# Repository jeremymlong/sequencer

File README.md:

# Sequencer
Inspired by the [LMNC Arduino 8 Step Sequencer Keyboard](https://www.lookmumnocomputer.com/sequencer-keyboard), but with several additional features.

## Specs
 * 0 to 5V range
 * Arduino Nano based
 * Selectable dual 8 steps or 16 steps
 * Arcade button style keyboard
 * Internal or external clock
 * Gate on/off selectable for every step
 * Gate output for every step
 * Reset input and switch
 * Selectable patterns
    * Off
    * Forward
    * Backward
    * Random
    * 1-2-3-4-3-2
    * 1-2-3-4-4-3-2-1
    * Forward 2x (1-1-2-2-3-3-4-4)
    * Backward 2x (4-4-3-3-2-2-1-1)
    * Clockwise
    * Counterclockwise

## BOM
| Part | Quantity | Link |
|------|------|------|
| Arduino Nano | 1 | [Tayda](https://www.taydaelectronics.com/nano-3-0-controller-compatible-with-arduino-nano-usb-driver.html) |
| CD4051 | 1 | [Tayda](https://www.taydaelectronics.com/cd4051-4051-ic-cmos-multiplex-demultiplexer.html) |
| 74HC595 | 2 | [Tayda](https://www.taydaelectronics.com/74hc595-8-bit-shift-register-ic.html) |
| Arcade button | 8 | [Amazon](https://a.co/d/00wVvfu) |
| Mini toggle SPDT | 2 | [Tayda](https://www.taydaelectronics.com/mini-toggle-switch-spdt-on-on.html) |
| Mini toggle SPDT (momentary) | 2 | [Tayda](https://www.taydaelectronics.com/momentary-mini-toggle-switch-spdt-on-off-on.html) |
| Mini toggle DPDT | 1 | [Tayda](https://www.taydaelectronics.com/mini-toggle-switch-dpdt-on-on.html) |
| 100nF Capacitor | 3 | [Tayda](https://www.taydaelectronics.com/0-1uf-100v-5-polyester-film-box-type-capacitor.html) |
| 1N4148 diode | 23 | [Tayda](https://www.taydaelectronics.com/1n4148-switching-signal-diode.html) |
| 5mm WS2811 F5 LED | 20 | [AliExpress](https://www.aliexpress.us/item/2251832527100547.html?gatewayAdapt=glo2usa4itemAdapt), [ebay](https://www.ebay.com/itm/225210423475?itmmeta=01HS53S4ZVHJHBY52T8WQZB1ET&hash=item346f9658b3:g:pUQAAOSwwGdf8ocz&itmprp=enc%3AAQAJAAAAwCDUYGcz5qj68xjJYhneY0VaI0AsSksXRR7zNsdxxVYPv%2BTpHbM6i6Cse7igi7r5pkI4ketezPmbqDTaU3huAlq58YY7W5qptqD56XkPZG7GSnOwLtegVyQoB51Hfvr%2BzgxCyjLdDuAnd0qzc8QuIPkxoM4O4NsTp0nrkO%2FBAysmSOFaF0JAeZIQaoKVNi9e1xnuLqgQoH9CKrZYwR4DYm8v4WXOQEnFtDER7cRtcld9aYo08zqe6yW89MqrQOQFFA%3D%3D%7Ctkp%3ABk9SR4jQ5KPJYw) |
| 12 position rotary switch | 1 | [Tayda](https://www.taydaelectronics.com/rotary-switch-1-pole-12-position-alpha-sr2611f.html) |
| 1k Resistor | 1 | [Tayda](https://www.taydaelectronics.com/10-x-resistor-1k-ohm-1-4w-1-metal-film-pkg-of-10.html) |
| 2k Resistor | 11 | [Tayda](https://www.taydaelectronics.com/resistor-2k-ohm-1-4w-1-metal-film-pkg-of-10.html) |
| 10k Resistor | 1 | [Tayda](https://www.taydaelectronics.com/10-x-resistor-10k-ohm-1-4w-1-metal-film-pkg-of-10.html) |
| 100k Resistor | 2 | [Tayda](https://www.taydaelectronics.com/10-x-resistor-100k-ohm-1-4w-1-metal-film-pkg-of-10.html) |
| 470k Resistor | 2 | [Tayda](https://www.taydaelectronics.com/10-x-resistor-470k-ohm-1-4w-1-metal-film-pkg-of-10.html) |
| 100k potentiometer | 17 | [Tayda](https://www.taydaelectronics.com/tayda-100k-ohm-linear-taper-potentiometer-with-solder-lugs.html) (panel wiring) |
| Mono jack | 7 (23 for per gate output) | [Tayda](https://www.taydaelectronics.com/pj-3001f-3-5-mm-mono-phone-jack.html) (pcb), [Tayda](https://www.taydaelectronics.com/3-5mm-earphone-mono-plug.html) (panel wiring) |
| Knobs | 18 |

## TODO
 * Arp when more than 1 button is held
 * Adjustable gate length

## Arduino Dependencies
 * [Adafruit_NeoPixel](https://github.com/adafruit/Adafruit_NeoPixel)

## Note about the schematic and board
Because this is big, I only did a small PCB for this. This is why there are random components floating above the board. For the remaining components (pots, buttons, switches, LEDs) I wired them old school with panel wiring. It was a great reminder why it's so much better to use a PCB for that instead.

## Note about 12 position switch
The 12 position switch is not on the schematic. It's wired like a potentiometer, with the 11 2k resistors between the positions. There are several tutorials on how to do this.

## Note about LEDs
The LEDs are not included on the schematic. I directly mounted the LEDs to the panel with hot glue and wired them point to point. Wires are connected to the leads of the first LED. The LEDs need to be wired in a particular order, as follows:
1. Step 1
1. Step 2
1. Step 3
1. Step 4
1. Step 5
1. Step 6
1. Step 7
1. Step 8
1. Step 16
1. Step 15
1. Step 14
1. Step 13
1. Step 12
1. Step 11
1. Step 10
1. Step 9
1. Clock out
1. Clock in
1. Gate A
1. Gate B

## Note about power
This really needs a clean power source. I'm powering mine from my rack's supply. If I power it from a regular cheap 5V switching adapter, it's noisy.

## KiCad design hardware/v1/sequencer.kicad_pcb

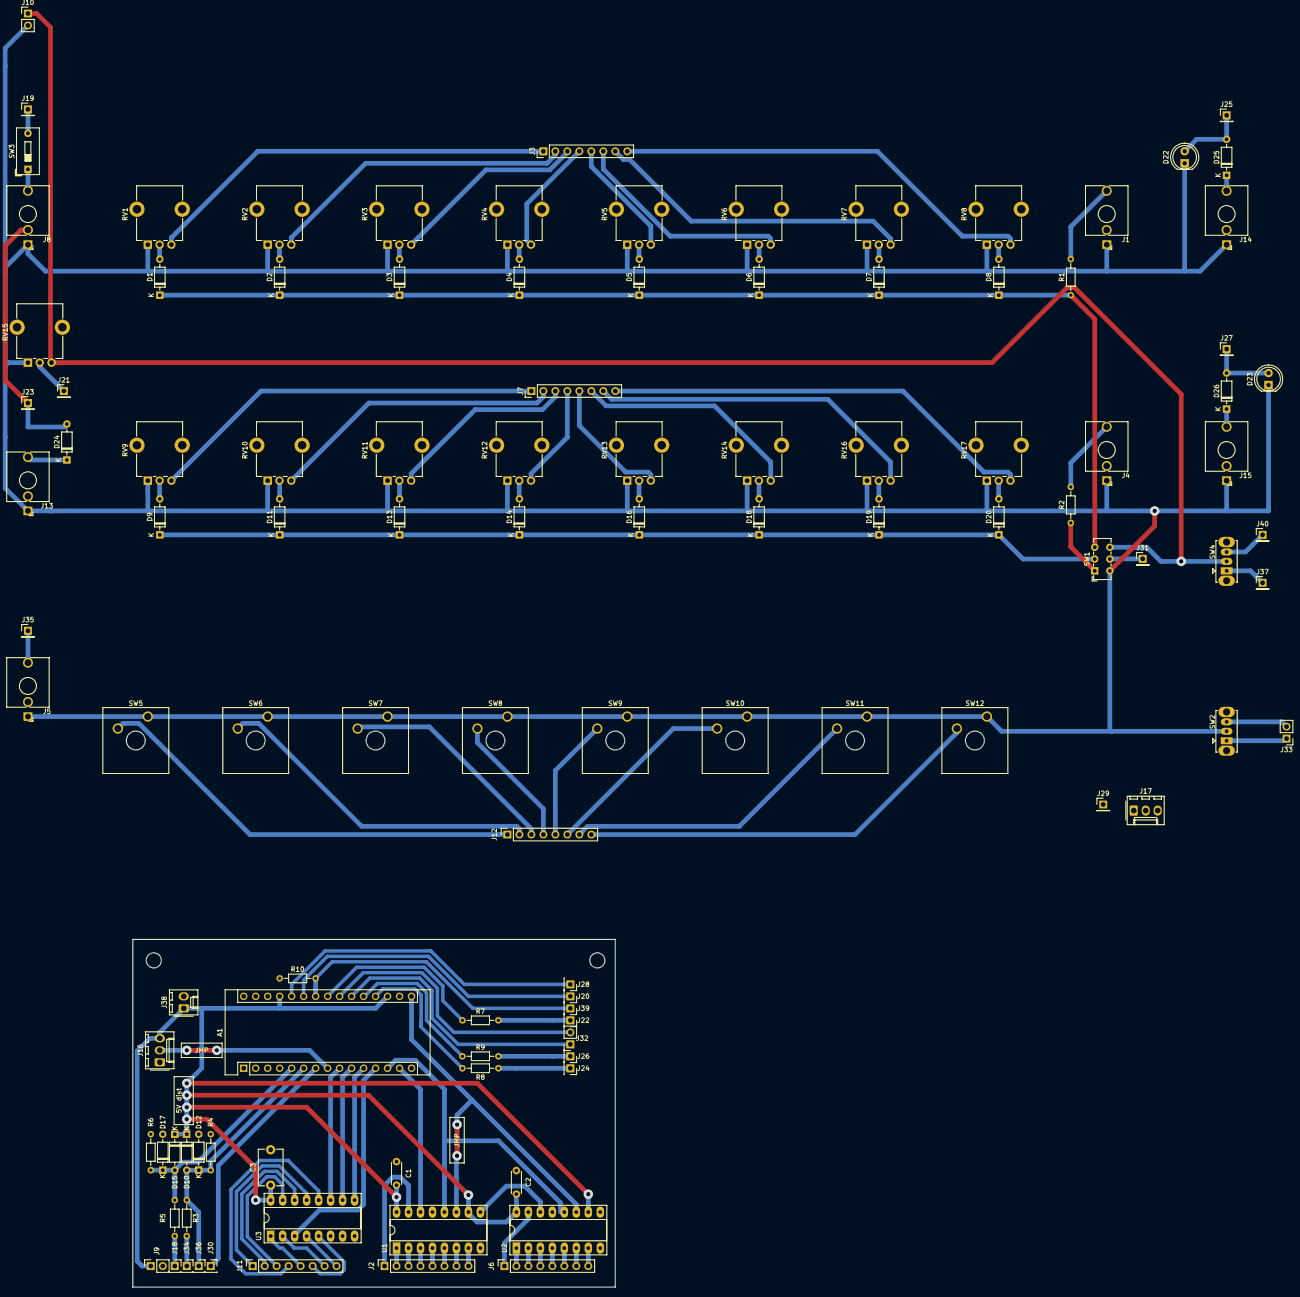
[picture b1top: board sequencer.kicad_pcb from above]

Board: 2 copper layers, 102.2 x 73.7 mm, 111 parts (0 on the bottom side), 113 nets.

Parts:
A1: Arduino_Nano_v3.x; Arduino_Nano
C1, C2: 100nF; C_Disc_D4.3mm_W1.9mm_P5.00mm
C3: 100nF; C_Disc_D7.5mm_W5.0mm_P7.50mm
D1, D2, D3, D4, D5, D6, D7, D8, D9, D10, D11, D12, D13, D14, D15, D16, D17, D18, D19, D20, D24, D25, D26: 1N4148; D_DO-35_SOD27_P7.62mm_Horizontal
D22, D23: LED; LED_D5.0mm
J1: CV A OUT; Jack_3.5mm_QingPu_WQP-PJ398SM_Vertical_CircularHoles
J2: seq_a_board; PinSocket_1x08_P2.54mm_Vertical
J3: seq_a_panel; PinHeader_1x08_P2.54mm_Vertical
J4: CV B OUT; Jack_3.5mm_QingPu_WQP-PJ398SM_Vertical_CircularHoles
J5: RESET_IN; Jack_3.5mm_QingPu_WQP-PJ398SM_Vertical_CircularHoles
J6: seq_b_board; PinSocket_1x08_P2.54mm_Vertical
J7: seq_b_panel; PinHeader_1x08_P2.54mm_Vertical
J8: CLOCK_IN; Jack_3.5mm_QingPu_WQP-PJ398SM_Vertical_CircularHoles
J9: power_board; PinSocket_1x02_P2.54mm_Vertical
J10: power_panel; PinHeader_1x02_P2.54mm_Vertical
J11: keys_board; PinSocket_1x08_P2.54mm_Vertical
J12: keys_panel; PinSocket_1x08_P2.54mm_Vertical
J13: CLOCK_OUT; Jack_3.5mm_QingPu_WQP-PJ398SM_Vertical_CircularHoles
J14: GATE A; Jack_3.5mm_QingPu_WQP-PJ398SM_Vertical_CircularHoles
J15: GATE B; Jack_3.5mm_QingPu_WQP-PJ398SM_Vertical_CircularHoles
J16: leds_board; Molex_KK-254_AE-6410-03A_1x03_P2.54mm_Vertical
J17: leds_wire; Molex_KK-254_AE-6410-03A_1x03_P2.54mm_Vertical
J18: CLK IN; PinSocket_1x01_P2.54mm_Vertical
J19, J21, J23, J25, J27, J29, J31, J35, J37, J40: panel; PinHeader_1x01_P2.54mm_Vertical
J20: CLK RATE; PinSocket_1x01_P2.54mm_Vertical
J22: CLK OUT; PinSocket_1x01_P2.54mm_Vertical
J24: GATE A; PinSocket_1x01_P2.54mm_Vertical
J26: GATE B; PinSocket_1x01_P2.54mm_Vertical
J28: SEQ MODE; PinSocket_1x01_P2.54mm_Vertical
J30: STEP CNT; PinSocket_1x01_P2.54mm_Vertical
J32: GATE PGM; PinSocket_1x02_P2.54mm_Vertical
J33: gate_pgm_panel; PinHeader_1x02_P2.54mm_Vertical
J34: RESET; PinSocket_1x01_P2.54mm_Vertical
J36: RST SW; PinSocket_1x01_P2.54mm_Vertical
J38: power_board_input; Molex_KK-254_AE-6410-02A_1x02_P2.54mm_Vertical
J39: STEP CNT SW; PinSocket_1x01_P2.54mm_Vertical
R1, R2, R7, R8, R9: 1k; R_Axial_DIN0204_L3.6mm_D1.6mm_P7.62mm_Horizontal
R3, R5: 100k; R_Axial_DIN0204_L3.6mm_D1.6mm_P7.62mm_Horizontal
R4, R6: 470k; R_Axial_DIN0204_L3.6mm_D1.6mm_P7.62mm_Horizontal
R10: 10k; R_Axial_DIN0204_L3.6mm_D1.6mm_P7.62mm_Horizontal
RV1: STEP1; Potentiometer_Alpha_RD901F-40-00D_Single_Vertical_CircularH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
RV2: STEP2; Potentiometer_Alpha_RD901F-40-00D_Single_Vertical_CircularH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
RV3: STEP3; Potentiometer_Alpha_RD901F-40-00D_Single_Vertical_CircularH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
RV4: STEP4; Potentiometer_Alpha_RD901F-40-00D_Single_Vertical_CircularH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
RV5: STEP5; Potentiometer_Alpha_RD901F-40-00D_Single_Vertical_CircularH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
RV6: STEP6; Potentiometer_Alpha_RD901F-40-00D_Single_Vertical_CircularH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
RV7: STEP7; Potentiometer_Alpha_RD901F-40-00D_Single_Vertical_CircularH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
RV8: STEP8; Potentiometer_Alpha_RD901F-40-00D_Single_Vertical_CircularH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
RV9: STEP1/9; Potentiometer_Alpha_RD901F-40-00D_Single_Vertical_CircularH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
RV10: STEP2/10; Potentiometer_Alpha_RD901F-40-00D_Single_Vertical_CircularH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
RV11: STEP3/11; Potentiometer_Alpha_RD901F-40-00D_Single_Vertical_CircularH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
RV12: STEP4/12; Potentiometer_Alpha_RD901F-40-00D_Single_Vertical_CircularH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
RV13: STEP5/13; Potentiometer_Alpha_RD901F-40-00D_Single_Vertical_CircularH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
RV14: STEP6/14; Potentiometer_Alpha_RD901F-40-00D_Single_Vertical_CircularH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
RV15: CLOCK; Potentiometer_Alpha_RD901F-40-00D_Single_Vertical_CircularH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
RV16: STEP7/15; Potentiometer_Alpha_RD901F-40-00D_Single_Vertical_CircularH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
RV17: STEP8/16; Potentiometer_Alpha_RD901F-40-00D_Single_Vertical_CircularH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
SW1: SW_DPDT_x2; SW_E-Switch_EG1271_DPDT
SW2, SW4: SW_SPDT_MSM; SW_Slide_1P2T_CK_OS102011MS2Q
SW3: SW_SPST; SW_DIP_SPSTx01_Slide_9.78x4.72mm_W7.62mm_P2.54mm
SW5, SW6, SW7, SW8, SW9, SW10, SW11, SW12: SW_Push; SW_Cherry_MX_1.00u_Plate
U1, U2: 74HC595; DIP-16_W7.62mm_Socket_LongPads
U3: 4051; DIP-16_W7.62mm_Socket_LongPads

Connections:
+5V: A1.18, A1.27, C1.1, C2.1, C3.1, D10.1, D15.1, J9.1, J16.3, J38.1, U1.10, U1.16, U2.10, U2.16, U3.16
+5VA: J10.1, RV15.3, SW1.6, SW4.2
GND: A1.4, A1.29, C1.2, C2.2, C3.2, D12.2, D17.2, J9.2, J16.1, J38.2, R4.1, R6.1, R10.1, U1.8, U1.13, U2.8, U2.13, U3.6, U3.7, U3.8
GNDA: D22.1, D23.1, J1.S, J4.S, J5.S, J8.S, J10.2, J13.S, J14.S, J15.S, RV1.1, RV2.1, RV3.1, RV4.1, RV5.1, RV6.1, RV7.1, RV8.1, RV9.1, RV10.1, RV11.1, RV12.1, RV13.1, RV14.1, RV15.1, RV16.1, RV17.1, SW1.4, SW2.2, SW5.1, SW6.1, SW7.1, SW8.1, SW9.1, SW10.1, SW11.1, SW12.1
MOSI: A1.14, U1.14
unnamed: D1.1, D2.1, D3.1, D4.1, D5.1, D6.1, D7.1, D8.1, R1.1, SW1.3
unnamed: D1.2, RV1.2
unnamed: D2.2, RV2.2
unnamed: D3.2, RV3.2
unnamed: D4.2, RV4.2
unnamed: D5.2, RV5.2
unnamed: D6.2, RV6.2
unnamed: D7.2, RV7.2
unnamed: D8.2, RV8.2
unnamed: D9.2, RV9.2
unnamed: D9.1, D11.1, D13.1, D14.1, D16.1, D18.1, D19.1, D20.1, SW1.2
unnamed: D11.2, RV10.2
unnamed: D13.2, RV11.2
unnamed: D14.2, RV12.2
unnamed: D16.2, RV13.2
unnamed: D18.2, RV14.2
unnamed: D19.2, RV16.2
unnamed: D20.2, RV17.2
unnamed: D22.2, D25.2, J25.1
unnamed: D23.2, D26.2, J27.1
unnamed: D24.1, J13.T
unnamed: D24.2, J8.TN, J23.1
unnamed: D25.1, J14.T
unnamed: D26.1, J15.T
unnamed: J1.T, R1.2
unnamed: J2.1, U1.15
unnamed: J2.2, U1.1
unnamed: J2.3, U1.2
unnamed: J2.4, U1.3
unnamed: J2.5, U1.4
unnamed: J2.6, U1.5
unnamed: J2.7, U1.6
unnamed: J2.8, U1.7
unnamed: J3.1, RV1.3
unnamed: J3.2, RV2.3
unnamed: J3.3, RV3.3
unnamed: J3.4, RV4.3
unnamed: J3.5, RV5.3
unnamed: J3.6, RV6.3
unnamed: J3.7, RV7.3
unnamed: J3.8, RV8.3
unnamed: J4.T, R2.2
unnamed: J6.1, U2.15
unnamed: J6.2, U2.1
unnamed: J6.3, U2.2
unnamed: J6.4, U2.3
unnamed: J6.5, U2.4
unnamed: J6.6, U2.5
unnamed: J6.7, U2.6
unnamed: J6.8, U2.7
unnamed: J7.1, RV9.3
unnamed: J7.2, RV10.3
unnamed: J7.3, RV11.3
unnamed: J7.4, RV12.3
unnamed: J7.5, RV13.3
unnamed: J7.6, RV14.3
unnamed: J7.7, RV16.3
unnamed: J7.8, RV17.3
unnamed: J8.T, SW3.1
unnamed: J11.1, U3.13
unnamed: J11.2, U3.14
unnamed: J11.3, U3.15
unnamed: J11.4, U3.12
unnamed: J11.5, U3.1
unnamed: J11.6, U3.5
unnamed: J11.7, U3.2
unnamed: J11.8, U3.4
unnamed: J12.1, SW5.2
unnamed: J12.2, SW6.2
unnamed: J12.3, SW7.2
unnamed: J12.4, SW8.2
unnamed: J12.5, SW9.2
unnamed: J12.6, SW10.2
unnamed: J12.7, SW11.2
unnamed: J12.8, SW12.2
unnamed: J18.1, R5.2
unnamed: J19.1, SW3.2
unnamed: J21.1, RV15.2
unnamed: J22.1, R7.2
unnamed: J24.1, R8.2
unnamed: J26.1, R9.2
unnamed: J31.1, SW1.5
unnamed: J33.1, SW2.1
unnamed: J33.2, SW2.3
unnamed: J34.1, R3.2
unnamed: J5.T, J35.1
unnamed: J37.1, SW4.1
unnamed: J40.1, SW4.3
unnamed: R2.1, SW1.1
unnamed: U1.9, U2.14
SCK: A1.16, U1.11, U2.11
clock_in: A1.5, D15.2, D17.1, R5.1, R6.2
clock_out: A1.23, R7.1
clock_rate: A1.25, J20.1
gate_a_program: A1.21, J32.1
gate_b_program: A1.22, J32.2
gate_output_a: A1.19, R8.1
gate_output_b: A1.20, R9.1
key_input: A1.12, U3.3
key_s0: A1.9, U3.11
key_s1: A1.10, U3.10
key_s2: A1.11, U3.9
led_data_out: A1.8, J16.2
select_595: A1.13, U1.12, U2.12
sequence_mode: A1.26, J28.1
sequence_reset: A1.6, D10.2, D12.1, J36.1, R3.1, R4.2
step_count: A1.7, J30.1
step_count_program: A1.24, J39.1, R10.2

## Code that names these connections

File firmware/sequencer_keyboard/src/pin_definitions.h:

#pragma once
#include <Arduino.h>


namespace sk {
namespace pins {
    static const int clock_output = A4;
    static const int clock_rate_pot = A6;
    static const int clock_input = 2;

    static const int sequence_reset = 3;
    static const int sequencer_output_select = 10;
    static const int sequence_mode = A7;
    
    static const int keyboard_input = 9;
    static const int keyboard_s0 = 6;
    static const int keyboard_s1 = 7;
    static const int keyboard_s2 = 8;

    static const int gate_output_a = A0;
    static const int gate_output_b = A1;
    static const int gate_program_a = A2;
    static const int gate_program_b = A3;

    static const int step_count = 4;
    static const int step_count_program = A5;

    static const int led_data_output = 5;
}
}

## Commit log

2024-03-17 Added readme
2024-03-17 Added gates image and power note to README
2024-03-17 Added note about board/schematic to README
